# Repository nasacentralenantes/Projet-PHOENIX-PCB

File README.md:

# Projet-PHOENIX-PCB
Electrical schematics for the PCB of the rocket

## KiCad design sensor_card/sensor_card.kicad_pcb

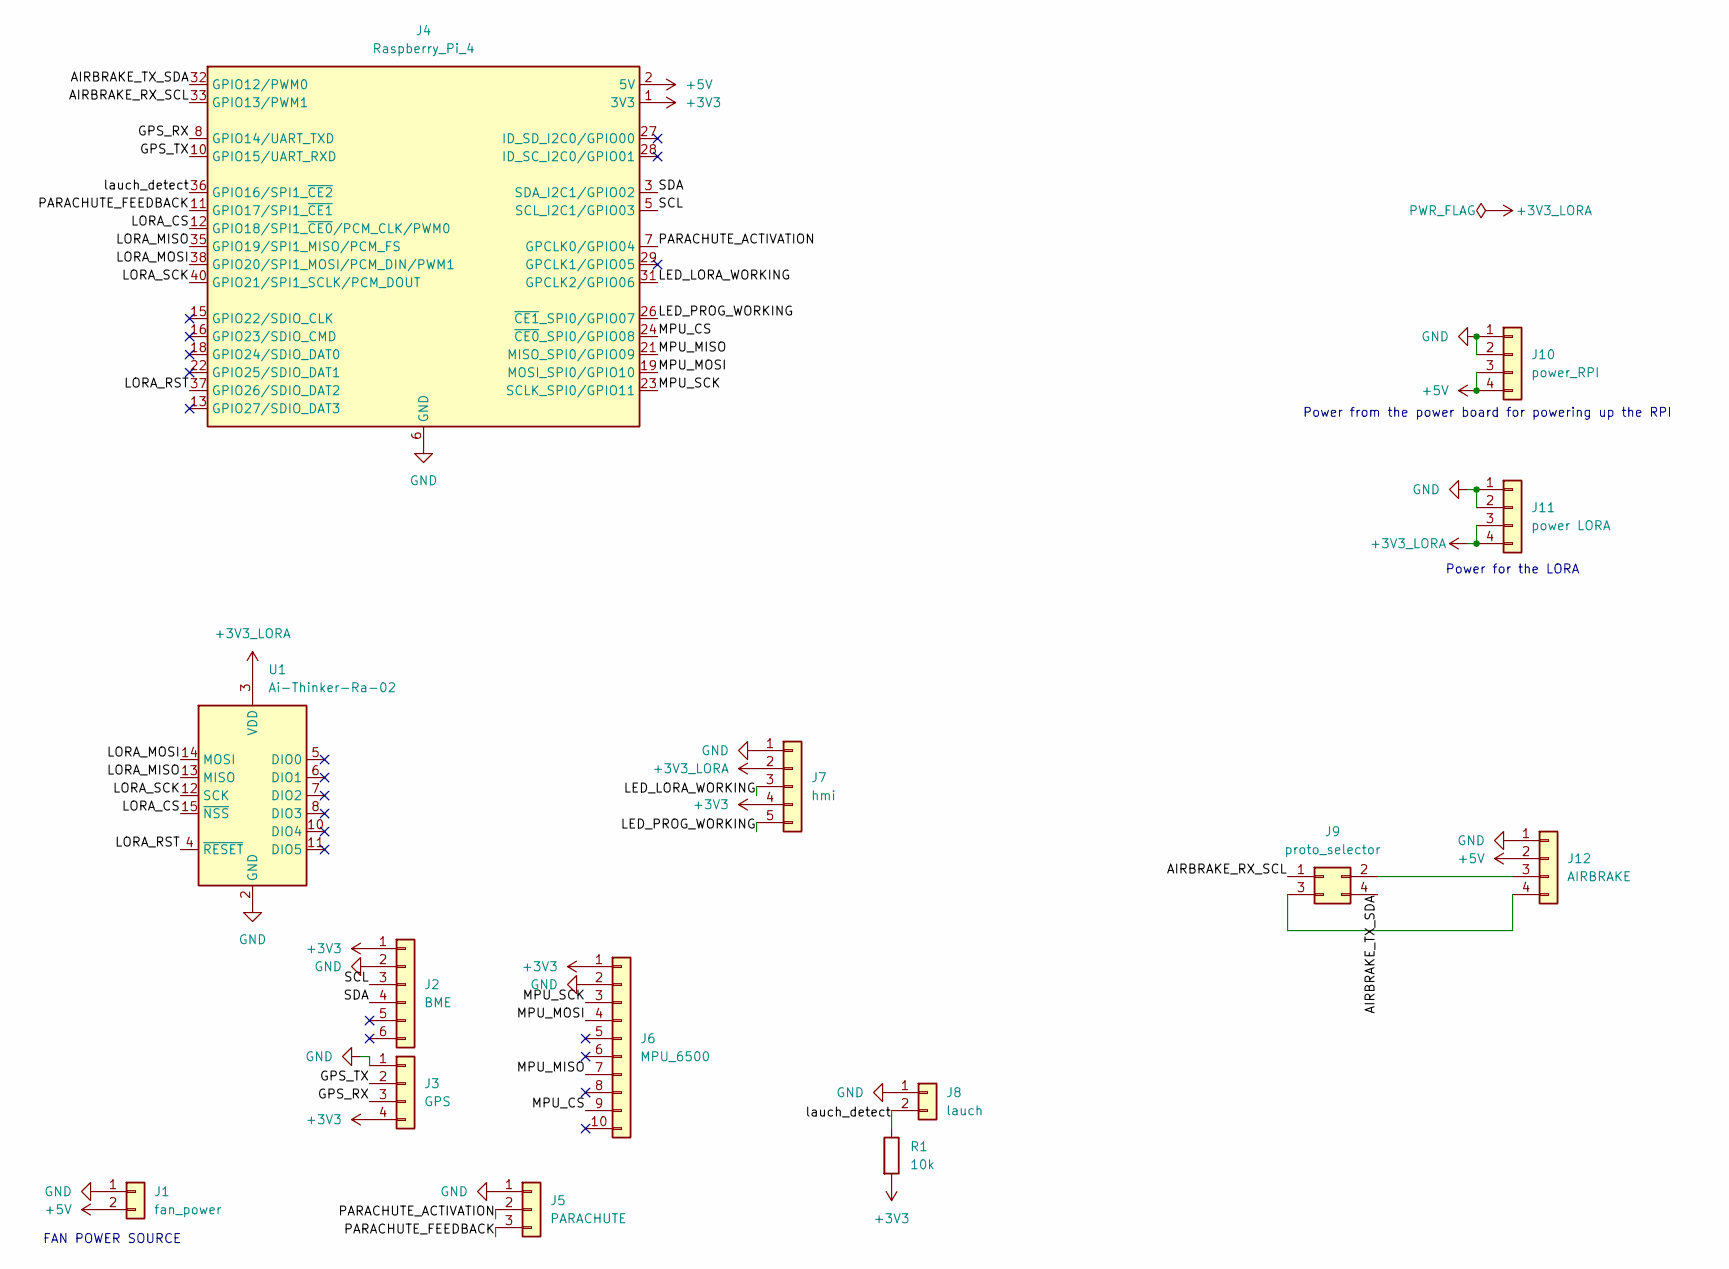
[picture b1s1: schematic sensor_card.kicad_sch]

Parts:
J1: fan_power; PinHeader_1x02_P2.54mm_Horizontal
J2: BME; BME280
J3: GPS
J4: Raspberry_Pi_4; PinSocket_2x20_P2.54mm_Vertical
J5: PARACHUTE; JST_XH_S3B-XH-A_1x03_P2.50mm_Horizontal
J6: MPU_6500; MPU6500
J7: hmi; JST_XH_S5B-XH-A_1x05_P2.50mm_Horizontal
J8: lauch; JST_XH_S2B-XH-A_1x02_P2.50mm_Horizontal
J9: proto_selector; PinHeader_2x02_P2.54mm_Vertical
J10: power_RPI; JST_XH_S4B-XH-A_1x04_P2.50mm_Horizontal
J11: power LORA; JST_XH_S4B-XH-A_1x04_P2.50mm_Horizontal
J12: AIRBRAKE; JST_XH_S4B-XH-A_1x04_P2.50mm_Horizontal
R1: 10k; R_Axial_DIN0204_L3.6mm_D1.6mm_P7.62mm_Horizontal
U1: Ai-Thinker-Ra-02; Ai-Thinker-Ra-01-LoRa

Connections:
+3V3: J2.1, J3.4, J4.1 (3V3), J4.17 (3V3), J6.1, J7.4, R1.2
+3V3_LORA: J7.2, J11.3, J11.4, U1.3 (VDD)
+5V: J1.2, J4.2 (5V), J4.4 (5V), J10.3, J10.4, J12.2
/AIRBRAKE_RX_SCL: J4.33 (GPIO13/PWM1), J9.1
/AIRBRAKE_TX_SDA: J4.32 (GPIO12/PWM0), J9.4
/GPS_RX: J3.3, J4.8 (GPIO14/UART_TXD)
/GPS_TX: J3.2, J4.10 (GPIO15/UART_RXD)
/LED_LORA_WORKING: J4.31 (GPCLK2/GPIO06), J7.3
/LED_PROG_WORKING: J4.26 (~CE1_SPI0/GPIO07), J7.5
/LORA_CS: J4.12 (GPIO18/SPI1_~CE0/PCM_CLK/PWM0), U1.15 (~NSS)
/LORA_MISO: J4.35 (GPIO19/SPI1_MISO/PCM_FS), U1.13 (MISO)
/LORA_MOSI: J4.38 (GPIO20/SPI1_MOSI/PCM_DIN/PWM1), U1.14 (MOSI)
/LORA_RST: J4.37 (GPIO26/SDIO_DAT2), U1.4 (~RESET)
/LORA_SCK: J4.40 (GPIO21/SPI1_SCLK/PCM_DOUT), U1.12 (SCK)
/MPU_CS: J4.24 (~CE0_SPI0/GPIO08), J6.9
/MPU_MISO: J4.21 (MISO_SPI0/GPIO09), J6.7
/MPU_MOSI: J4.19 (MOSI_SPI0/GPIO10), J6.4
/MPU_SCK: J4.23 (SCLK_SPI0/GPIO11), J6.3
/PARACHUTE_ACTIVATION: J4.7 (GPCLK0/GPIO04), J5.2
/PARACHUTE_FEEDBACK: J4.11 (GPIO17/SPI1_~CE1), J5.3
/SCL: J2.3, J4.5 (SCL_I2C1/GPIO03)
/SDA: J2.4, J4.3 (SDA_I2C1/GPIO02)
/lauch_detect: J4.36 (GPIO16/SPI1_~CE2), J8.2, R1.1
GND: J1.1, J2.2, J3.1, J4.6 (GND), J4.9 (GND), J4.14 (GND), J4.20 (GND), J4.25 (GND), J4.30 (GND), J4.34 (GND), J4.39 (GND), J5.1, J6.2, J7.1, J8.1, J10.1, J10.2, J11.1, J11.2, J12.1, U1.1 (GND), U1.2 (GND), U1.9 (GND), U1.16 (GND)
unnamed: J9.2, J12.3
unnamed: J9.3, J12.4

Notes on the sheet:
Power for the LORA
Power from the power board for powering up the RPI
FAN POWER SOURCE

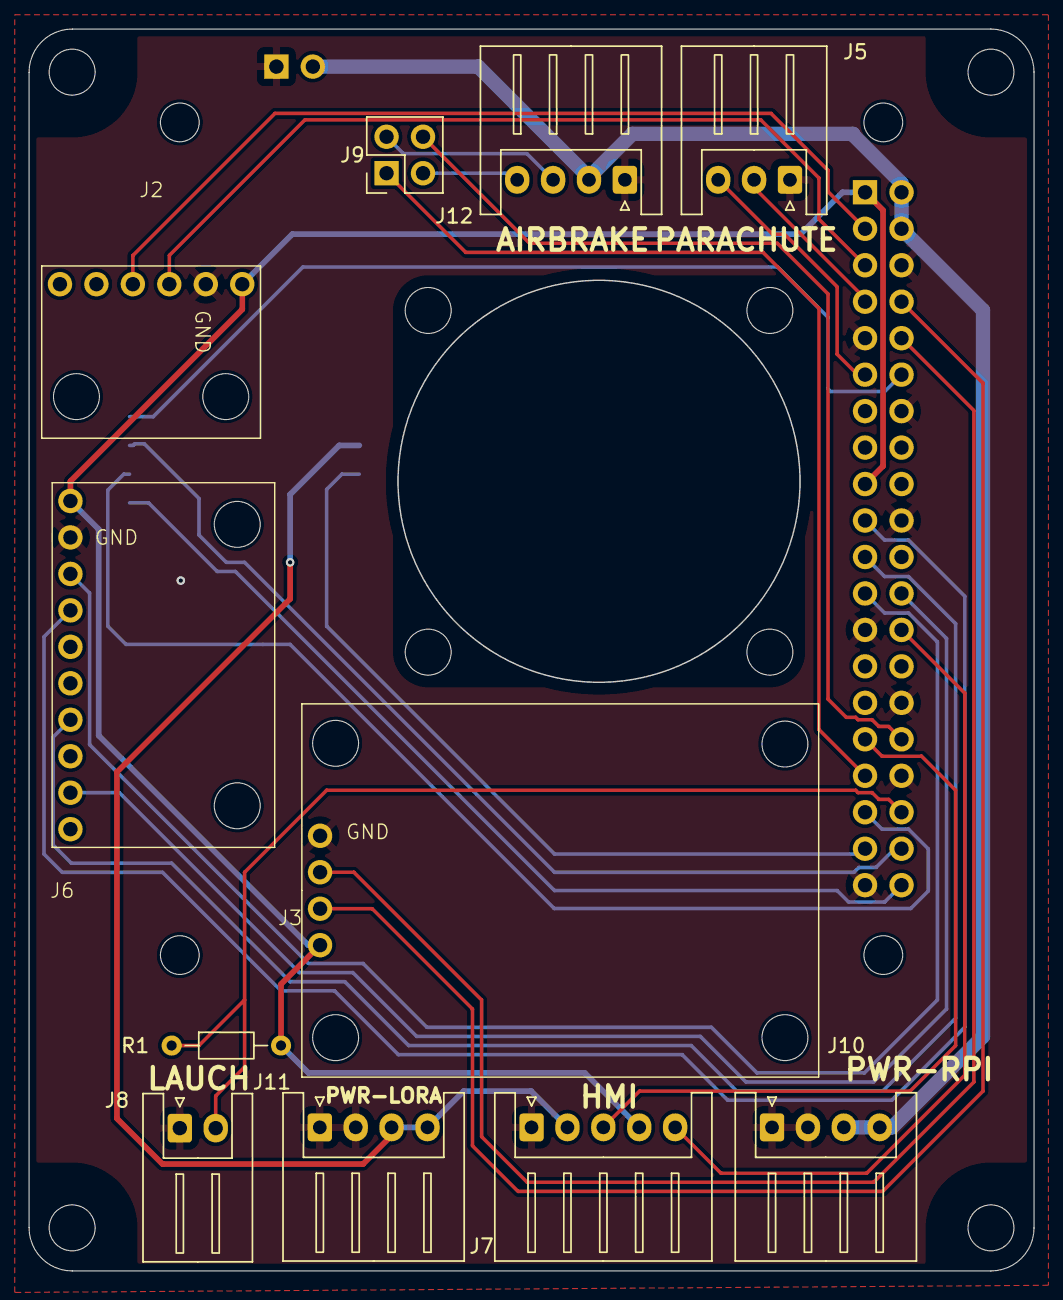
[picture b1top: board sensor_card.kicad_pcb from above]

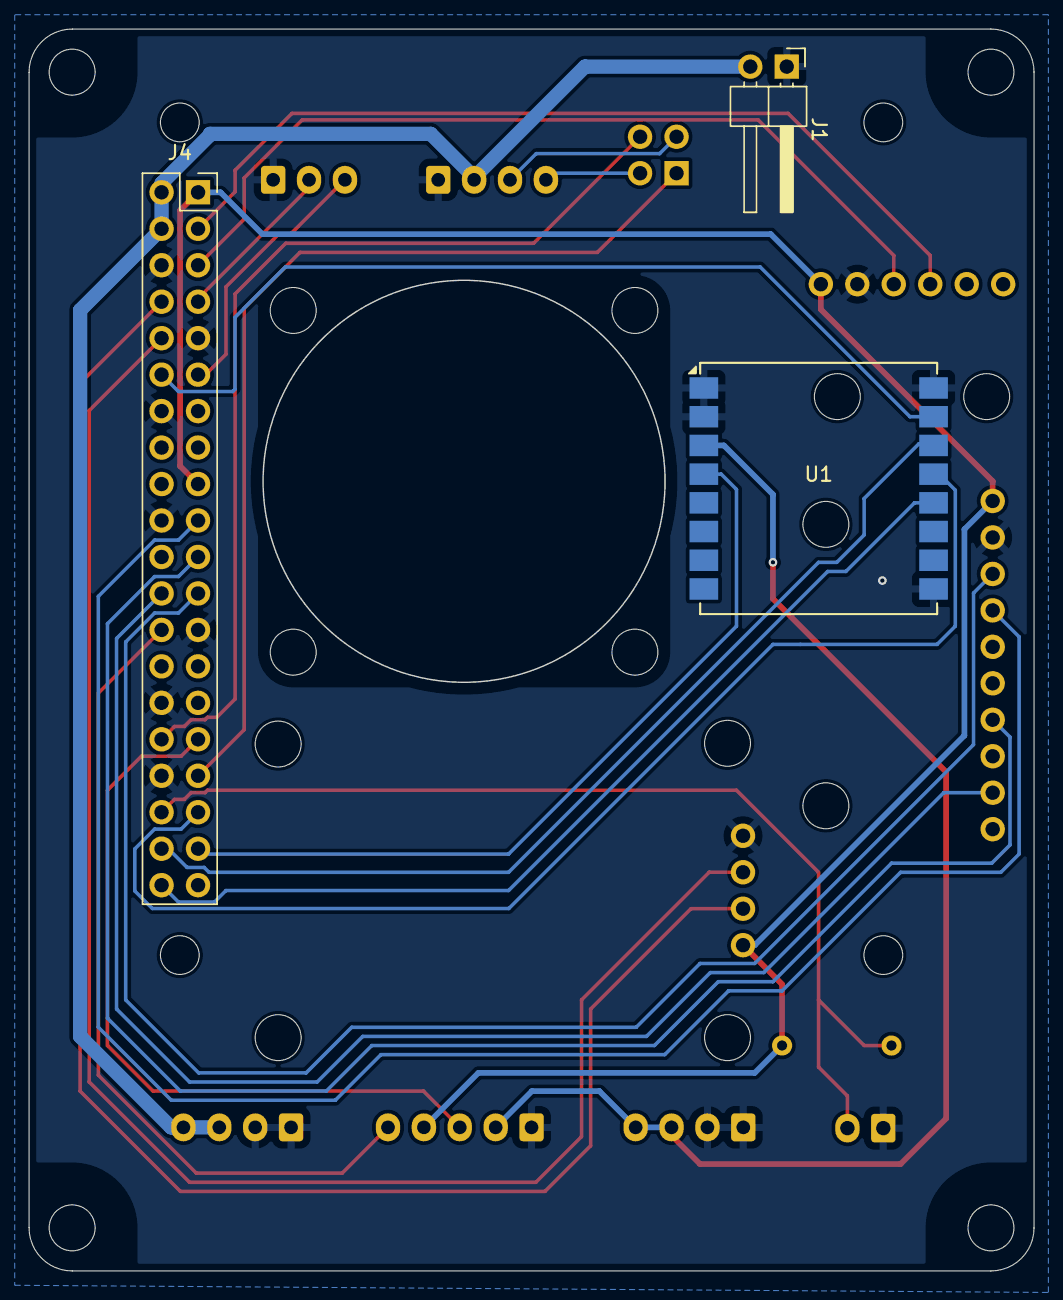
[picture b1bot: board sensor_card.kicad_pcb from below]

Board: 2 copper layers, 69.9 x 86.4 mm, 22 parts (3 on the bottom side), 26 nets.

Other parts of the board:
H1, H2, H3, H4: MountingHole_3.2mm_M3
H5, H6, H7, H8: MountingHole_2.7mm_M2.5

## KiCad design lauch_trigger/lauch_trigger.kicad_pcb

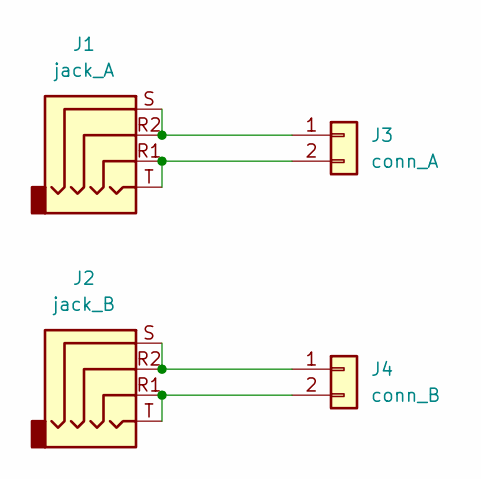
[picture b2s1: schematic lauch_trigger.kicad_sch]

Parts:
J1: jack_A; Jack_3.5mm_PJ320D_Horizontal
J2: jack_B; Jack_3.5mm_PJ320D_Horizontal
J3: conn_A; JST_XH_B2B-XH-A_1x02_P2.50mm_Vertical
J4: conn_B; JST_XH_B2B-XH-A_1x02_P2.50mm_Vertical

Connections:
unnamed: J1.R2, J1.S, J3.1
unnamed: J1.R1, J1.T, J3.2
unnamed: J2.R2, J2.S, J4.1
unnamed: J2.R1, J2.T, J4.2

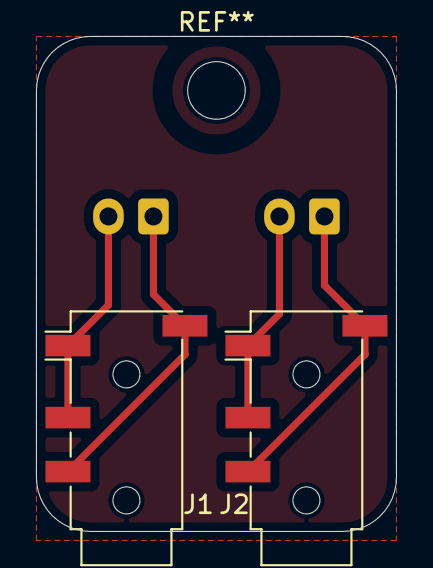
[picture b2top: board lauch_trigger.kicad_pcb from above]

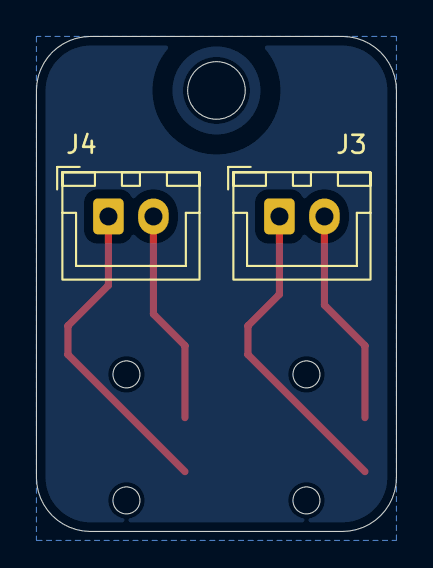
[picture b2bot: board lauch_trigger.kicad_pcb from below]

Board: 2 copper layers, 20.0 x 27.5 mm, 4 parts (2 on the bottom side), 4 nets.

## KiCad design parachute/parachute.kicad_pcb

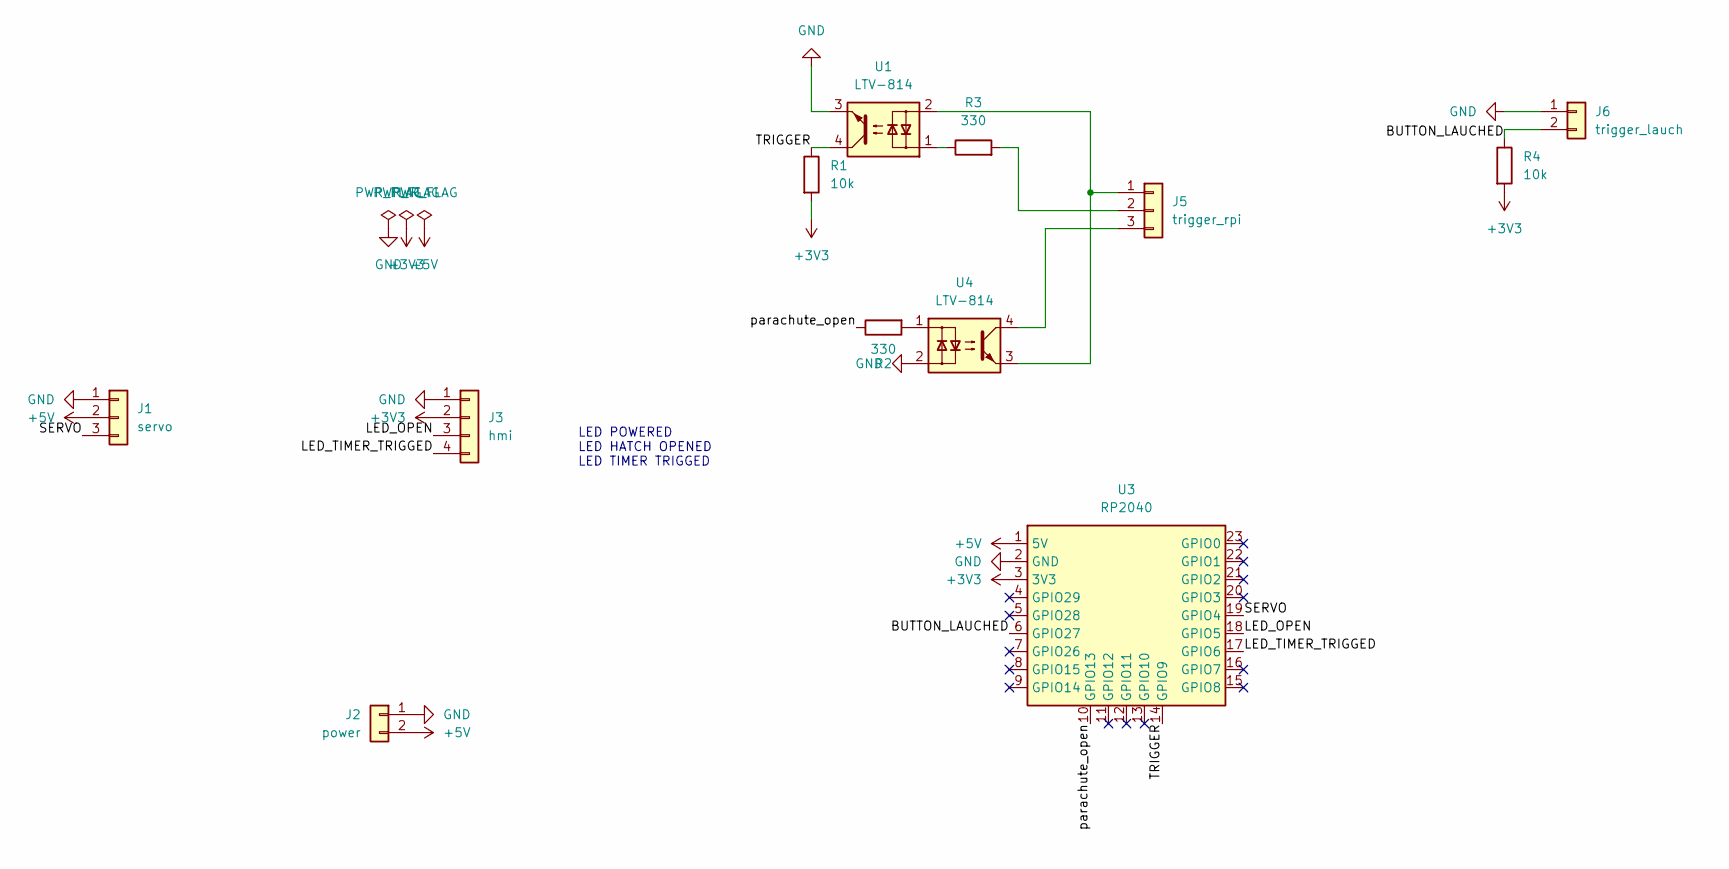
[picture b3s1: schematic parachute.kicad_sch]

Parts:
J1: servo; PinHeader_1x03_P2.54mm_Horizontal
J2: power; JST_XH_B2B-XH-A_1x02_P2.50mm_Vertical
J3: hmi; JST_XH_B4B-XH-A_1x04_P2.50mm_Vertical
J5: trigger_rpi; JST_XH_B3B-XH-A_1x03_P2.50mm_Vertical
J6: trigger_lauch; JST_XH_B2B-XH-A_1x02_P2.50mm_Vertical
R1, R4: 10k; R_Axial_DIN0204_L3.6mm_D1.6mm_P7.62mm_Horizontal
R2, R3: 330; R_Axial_DIN0204_L3.6mm_D1.6mm_P7.62mm_Horizontal
U1, U4: LTV-814; DIP-4_W7.62mm
U3: RP2040; rp2040_pico

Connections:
+3V3: J3.2, R1.2, R4.2, U3.3 (3V3)
+5V: J1.2, J2.2, U3.1 (5V)
/BUTTON_LAUCHED: J6.2, R4.1, U3.6 (GPIO27)
/LED_OPEN: J3.3, U3.18 (GPIO5)
/LED_TIMER_TRIGGED: J3.4, U3.17 (GPIO6)
/SERVO: J1.3, U3.19 (GPIO4)
/TRIGGER: R1.1, U1.4, U3.14 (GPIO9)
/parachute_open: R2.1, U3.10 (GPIO13)
GND: J1.1, J2.1, J3.1, J6.1, U1.3, U3.2 (GND), U4.2
unnamed: J5.1, U1.2, U4.3
unnamed: J5.2, R3.2
unnamed: J5.3, U4.4
unnamed: R2.2, U4.1
unnamed: R3.1, U1.1

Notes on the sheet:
LED POWERED LED HATCH OPENED LED TIMER TRIGGED

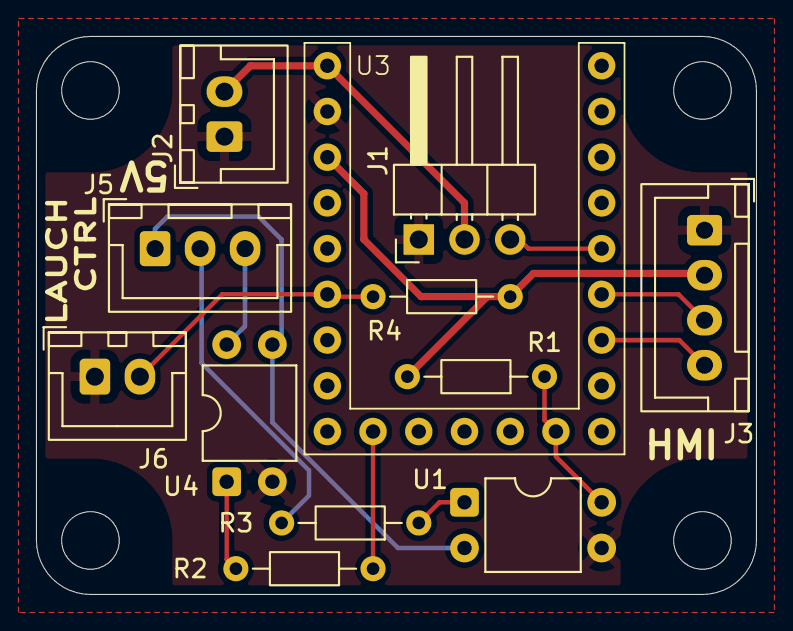
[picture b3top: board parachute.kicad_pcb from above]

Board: 2 copper layers, 40.0 x 31.0 mm, 16 parts (0 on the bottom side), 14 nets.

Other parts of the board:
H1, H2, H3, H4: MountingHole_3.2mm_M3_ISO7380

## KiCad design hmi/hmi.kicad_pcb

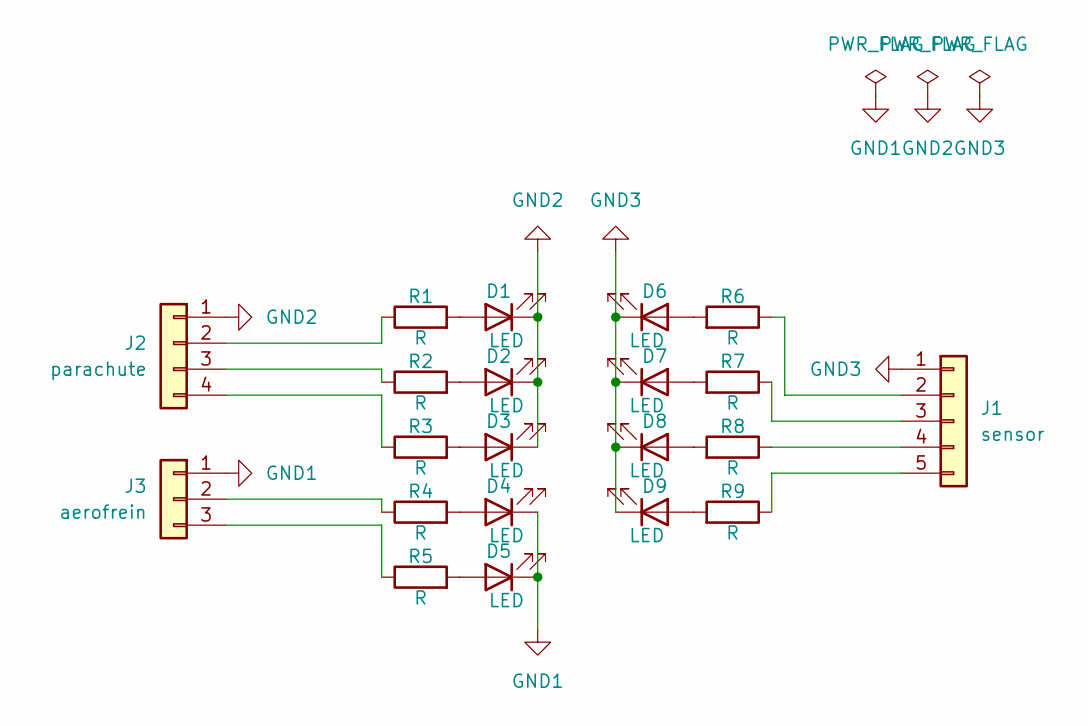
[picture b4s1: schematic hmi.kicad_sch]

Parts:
D1, D2, D3, D4, D5, D6, D7, D8, D9: LED; LED_D5.0mm_Clear
J1: sensor; JST_XH_S5B-XH-A_1x05_P2.50mm_Horizontal
J2: parachute; JST_XH_S4B-XH-A_1x04_P2.50mm_Horizontal
J3: aerofrein; JST_XH_S3B-XH-A_1x03_P2.50mm_Horizontal
R1, R2, R3, R4, R5, R6, R7, R8, R9: R; R_Axial_DIN0204_L3.6mm_D1.6mm_P7.62mm_Horizontal

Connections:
GND1: D4.1 (K), D5.1 (K), J3.1
GND2: D1.1 (K), D2.1 (K), D3.1 (K), J2.1
GND3: D6.1 (K), D7.1 (K), D8.1 (K), D9.1 (K), J1.1
unnamed: D1.2 (A), R1.2
unnamed: D2.2 (A), R2.2
unnamed: D3.2 (A), R3.2
unnamed: D4.2 (A), R4.2
unnamed: D5.2 (A), R5.2
unnamed: D6.2 (A), R6.2
unnamed: D7.2 (A), R7.2
unnamed: D8.2 (A), R8.2
unnamed: D9.2 (A), R9.2
unnamed: J1.2, R6.1
unnamed: J1.3, R7.1
unnamed: J1.4, R8.1
unnamed: J1.5, R9.1
unnamed: J2.2, R1.1
unnamed: J2.3, R2.1
unnamed: J2.4, R3.1
unnamed: J3.2, R4.1
unnamed: J3.3, R5.1

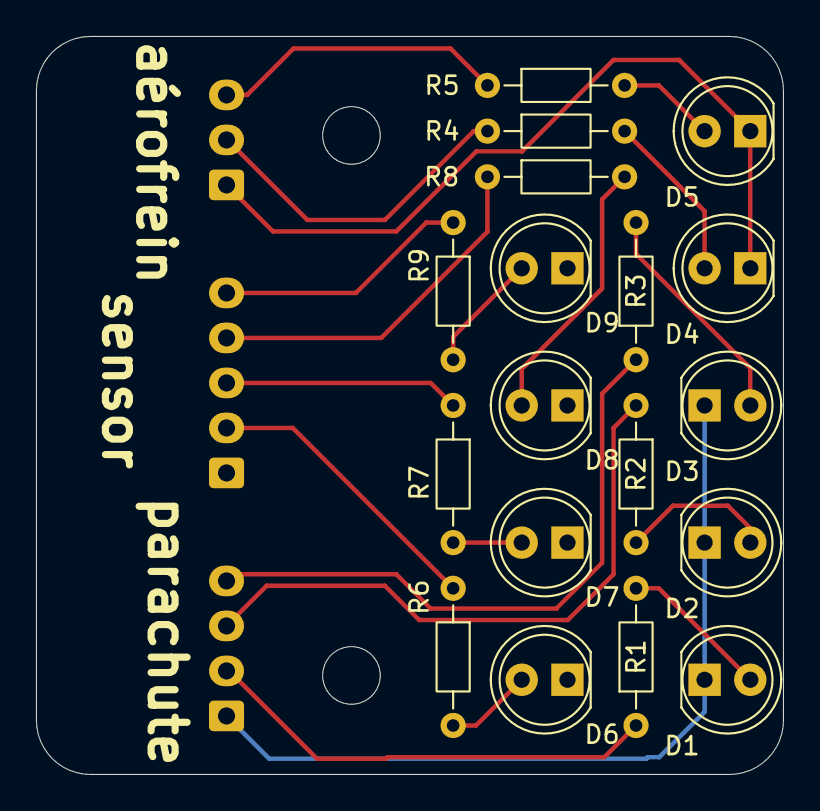
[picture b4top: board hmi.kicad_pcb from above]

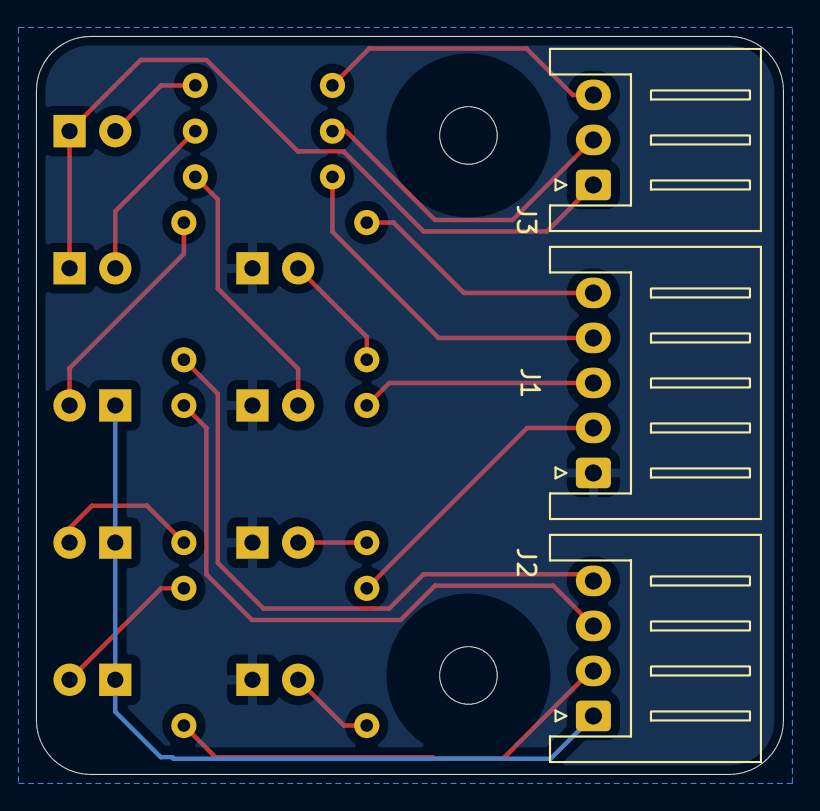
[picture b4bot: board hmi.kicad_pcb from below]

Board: 2 copper layers, 41.5 x 41.0 mm, 23 parts (3 on the bottom side), 21 nets.

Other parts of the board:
H1, H2: MountingHole_3.2mm_M3

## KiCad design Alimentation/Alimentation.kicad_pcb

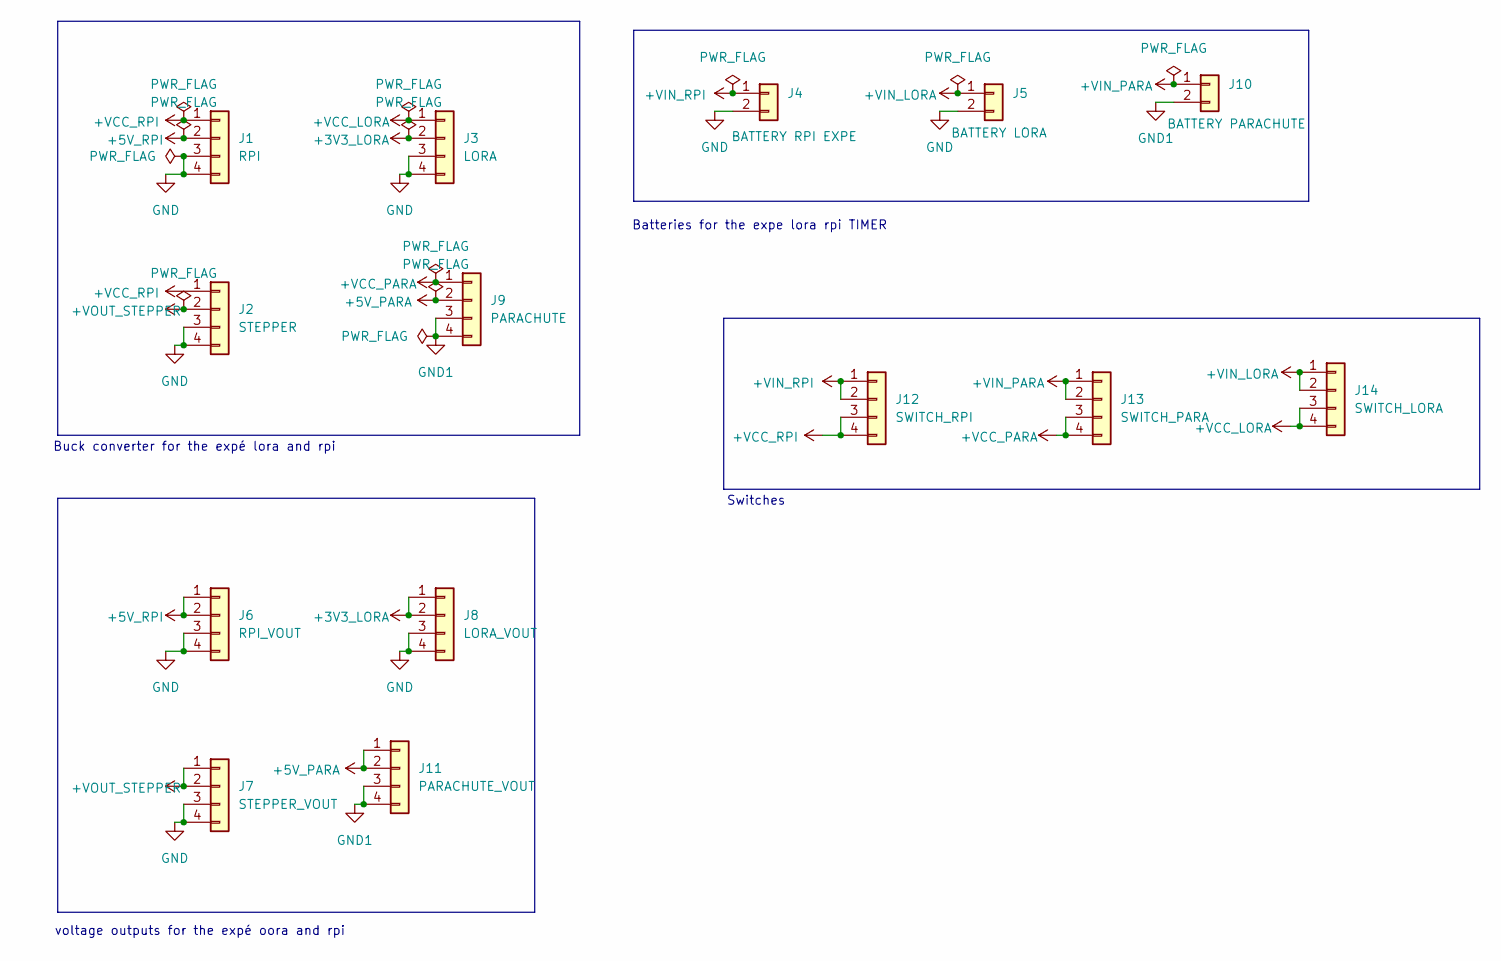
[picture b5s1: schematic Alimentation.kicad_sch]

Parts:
J1: RPI; LM2596
J2: STEPPER; LM2596
J3: LORA; LM2596
J4: BATTERY RPI EXPE; AMASS_XT60PW-M_1x02_P7.20mm_Horizontal
J5: BATTERY LORA; AMASS_XT60PW-M_1x02_P7.20mm_Horizontal
J6: RPI_VOUT; JST_XH_S4B-XH-A_1x04_P2.50mm_Horizontal
J7: STEPPER_VOUT; JST_XH_S4B-XH-A_1x04_P2.50mm_Horizontal
J8: LORA_VOUT; JST_XH_S4B-XH-A_1x04_P2.50mm_Horizontal
J9: PARACHUTE; LM2596
J10: BATTERY PARACHUTE; AMASS_XT60PW-M_1x02_P7.20mm_Horizontal
J11: PARACHUTE_VOUT; JST_XH_S4B-XH-A_1x04_P2.50mm_Horizontal
J12: SWITCH_RPI; JST_XH_B4B-XH-A_1x04_P2.50mm_Vertical
J13: SWITCH_PARA; JST_XH_B4B-XH-A_1x04_P2.50mm_Vertical
J14: SWITCH_LORA; JST_XH_B4B-XH-A_1x04_P2.50mm_Vertical

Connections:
+3V3_LORA: J3.2, J8.1, J8.2
+5V_PARA: J9.2, J11.1, J11.2
+5V_RPI: J1.2, J6.1, J6.2
+VCC_LORA: J3.1, J14.3, J14.4
+VCC_PARA: J9.1, J13.3, J13.4
+VCC_RPI: J1.1, J2.1, J12.3, J12.4
+VIN_LORA: J5.1, J14.1, J14.2
+VIN_PARA: J10.1, J13.1, J13.2
+VIN_RPI: J4.1, J12.1, J12.2
+VOUT_STEPPER: J2.2, J7.1, J7.2
GND: J1.3, J1.4, J2.3, J2.4, J3.3, J3.4, J4.2, J5.2, J6.3, J6.4, J7.3, J7.4, J8.3, J8.4
GND1: J9.3, J9.4, J10.2, J11.3, J11.4

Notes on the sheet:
Switches
Batteries for the expe lora rpi TIMER
voltage outputs for the expé oora and rpi
Buck converter for the expé lora and rpi

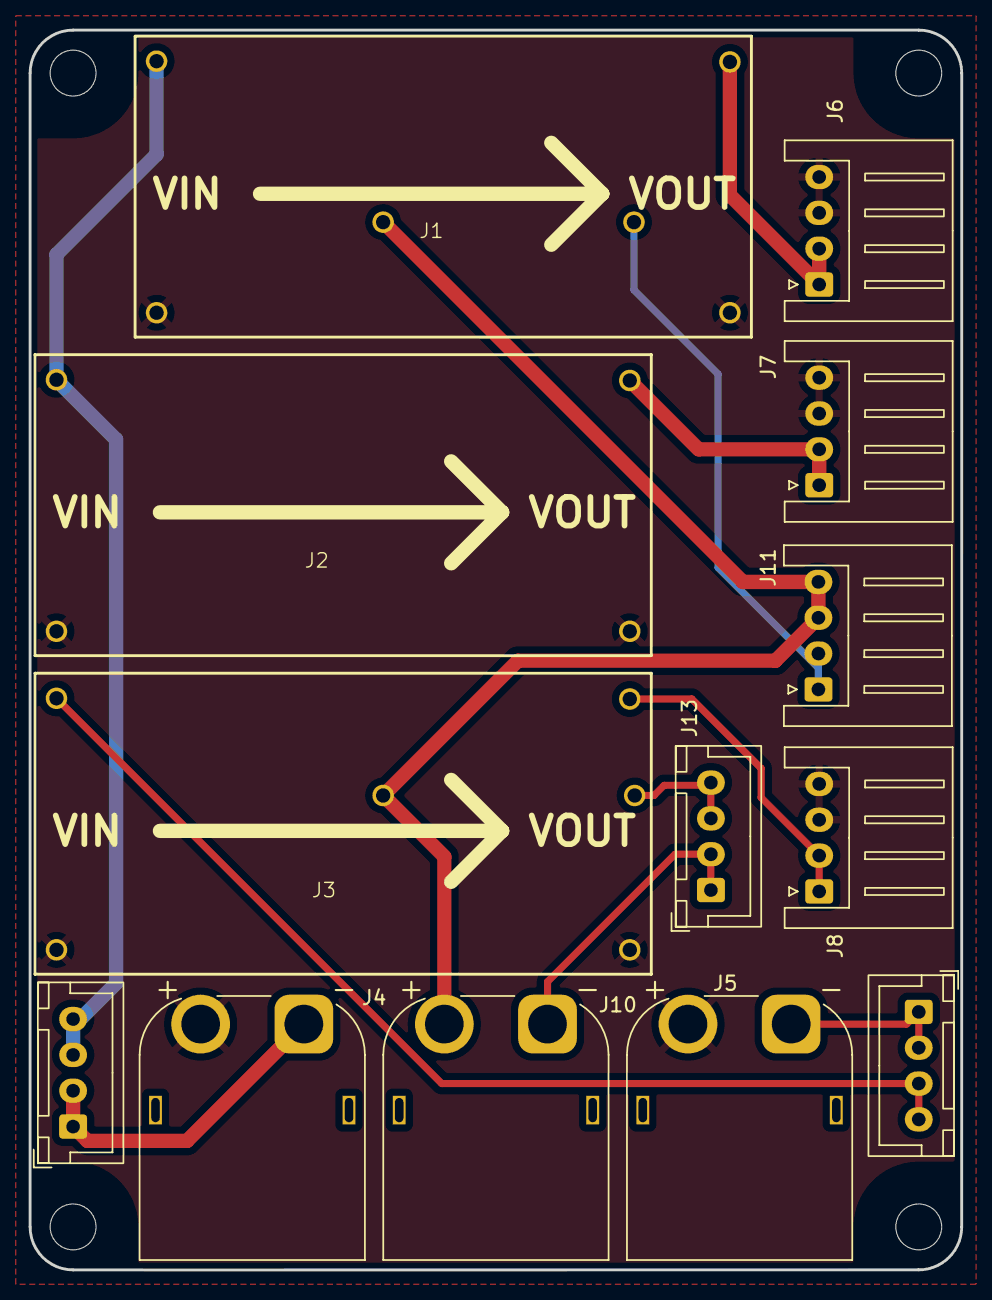
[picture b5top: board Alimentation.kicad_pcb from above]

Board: 2 copper layers, 65.0 x 86.5 mm, 18 parts (1 on the bottom side), 12 nets.

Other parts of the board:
H1, H2, H5, H6: MountingHole_3.2mm_M3

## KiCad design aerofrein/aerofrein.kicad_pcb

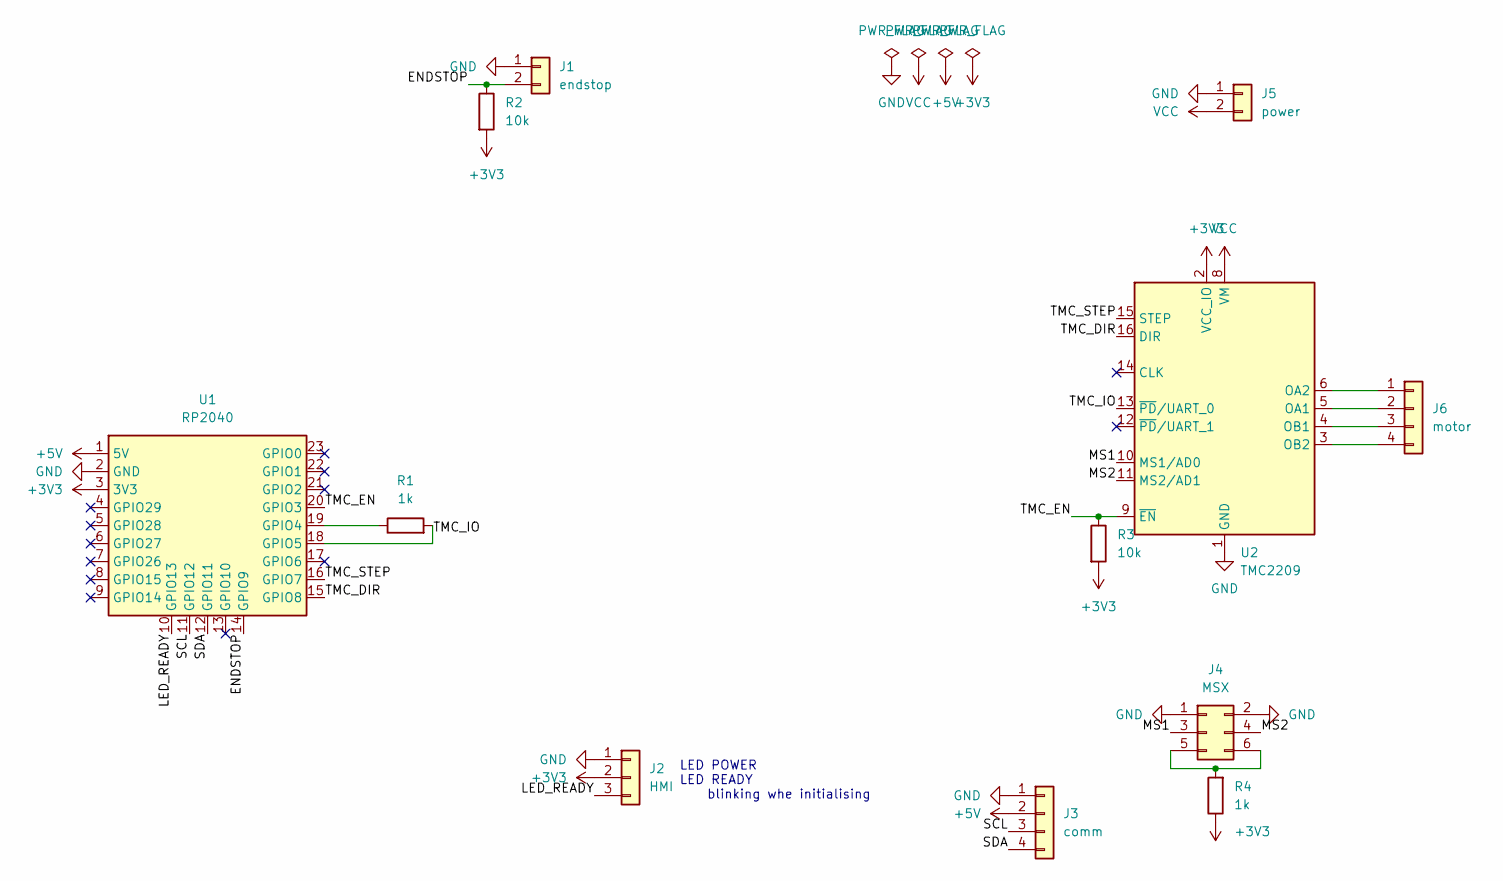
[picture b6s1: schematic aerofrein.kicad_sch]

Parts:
J1: endstop; JST_XH_B2B-XH-A_1x02_P2.50mm_Vertical
J2: HMI; JST_XH_B3B-XH-A_1x03_P2.50mm_Vertical
J3: comm; JST_XH_B4B-XH-A_1x04_P2.50mm_Vertical
J4: MSX; PinHeader_2x03_P2.54mm_Vertical
J5: power; JST_XH_B2B-XH-A_1x02_P2.50mm_Vertical
J6: motor; JST_XH_B4B-XH-A_1x04_P2.50mm_Vertical
R1, R4: 1k; R_Axial_DIN0204_L3.6mm_D1.6mm_P7.62mm_Horizontal
R2, R3: 10k; R_Axial_DIN0204_L3.6mm_D1.6mm_P7.62mm_Horizontal
U1: RP2040; rp2040_pico
U2: TMC2209; TMC2209 driver

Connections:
+3V3: J2.2, R2.2, R3.2, R4.1, U1.3 (3V3), U2.2 (VCC_IO)
+5V: J3.2, U1.1 (5V)
/ENDSTOP: J1.2, R2.1, U1.14 (GPIO9)
/LED_READY: J2.3, U1.10 (GPIO13)
/MS1: J4.3, U2.10 (MS1/AD0)
/MS2: J4.4, U2.11 (MS2/AD1)
/SCL: J3.3, U1.11 (GPIO12)
/SDA: J3.4, U1.12 (GPIO11)
/TMC_DIR: U1.15 (GPIO8), U2.16 (DIR)
/TMC_EN: R3.1, U1.20 (GPIO3), U2.9 (~EN)
/TMC_IO: R1.2, U1.18 (GPIO5), U2.13 (~PD/UART_0)
/TMC_STEP: U1.16 (GPIO7), U2.15 (STEP)
GND: J1.1, J2.1, J3.1, J4.1, J4.2, J5.1, U1.2 (GND), U2.1 (GND), U2.7 (GND)
unnamed: J4.5, J4.6, R4.2
unnamed: J6.1, U2.6 (OA2)
unnamed: J6.2, U2.5 (OA1)
unnamed: J6.3, U2.4 (OB1)
unnamed: J6.4, U2.3 (OB2)
unnamed: R1.1, U1.19 (GPIO4)
VCC: J5.2, U2.8 (VM)

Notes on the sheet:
LED POWER LED READY blinking whe initialising

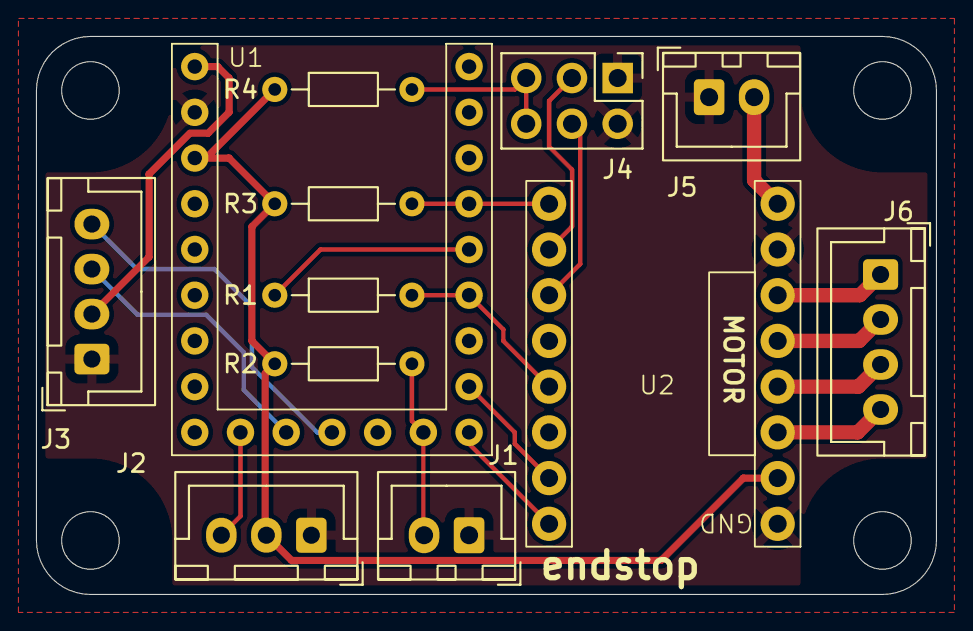
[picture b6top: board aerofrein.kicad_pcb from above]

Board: 2 copper layers, 50.0 x 31.0 mm, 16 parts (0 on the bottom side), 20 nets.

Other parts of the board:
H1, H1#2, H1#3, H1#4: MountingHole_3.2mm_M3_ISO7380

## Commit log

2026-01-30 Testing Cloning . Resistor added
2026-02-02 finition des aérofreins
2026-02-02 Ajout de la library local
2026-02-03 ajout d'une carte hmi
2026-02-03 moved component
2026-02-03 update parachute to have back information
2026-02-03 Sensor Board Fully Connected
2026-02-03 Updated Sensor PCB
2026-02-03 Board Routed Prototype 1 . Power Routes to be redone
2026-02-04 added card for the jack connector
2026-02-04 created the pcb
2026-02-04 Power board added
2026-02-04 Routed Power Board
2026-02-06 Update airbrakes PCB
2026-02-09 mise à jour de l'empreinte
2026-02-09 création de la carte PCB aérofrein
2026-02-09 correction PCB
2026-02-09 mise à jour du circuit du parachute, début de la création de la carte PCB
2026-02-10 agencement et piste cuivre pour PCB parachute
2026-02-10 added copper area
2026-02-11 Created PCB for jack connectors
2026-02-11 created footprint for jack connector
2026-02-11 update gitignore to ignore step file except for footprints
2026-02-14 pcb for hmi
2026-03-03 Fully Routed Sensor board
2026-03-03 flipped connections for the GPS connector to 3_3,RX <-> GND,TX
2026-03-03 Fully routed power board
2026-03-07 update gitignore
2026-03-15 airbrake full revision
2026-03-15 alimentation: full revision
2026-03-15 added footprint for lm2596 (with 3D model), bme280, mpu6500, gps
2026-03-15 hmi full revision
2026-03-15 parachute full revision
2026-03-15 lauch trigger: full revision
2026-03-15 sensor card: full revision
